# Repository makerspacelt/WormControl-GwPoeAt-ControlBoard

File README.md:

---

WormControl Gateway POE.AT

NOTE: This is only a prototype now, so things might not work and everything might change 

Basic target features:

* Compatibility with esphome and Home Assistant

Dev NOTE: before commit, run `./kibot.sh` to regenerate documentation, bom, gerbers and other assets.

* [schematics.pdf](gen/schematics.pdf)
* [pcb.pdf with dimensions](gen/pcb.pdf)
* [ibom.html](gen/single/ibom.html)

---

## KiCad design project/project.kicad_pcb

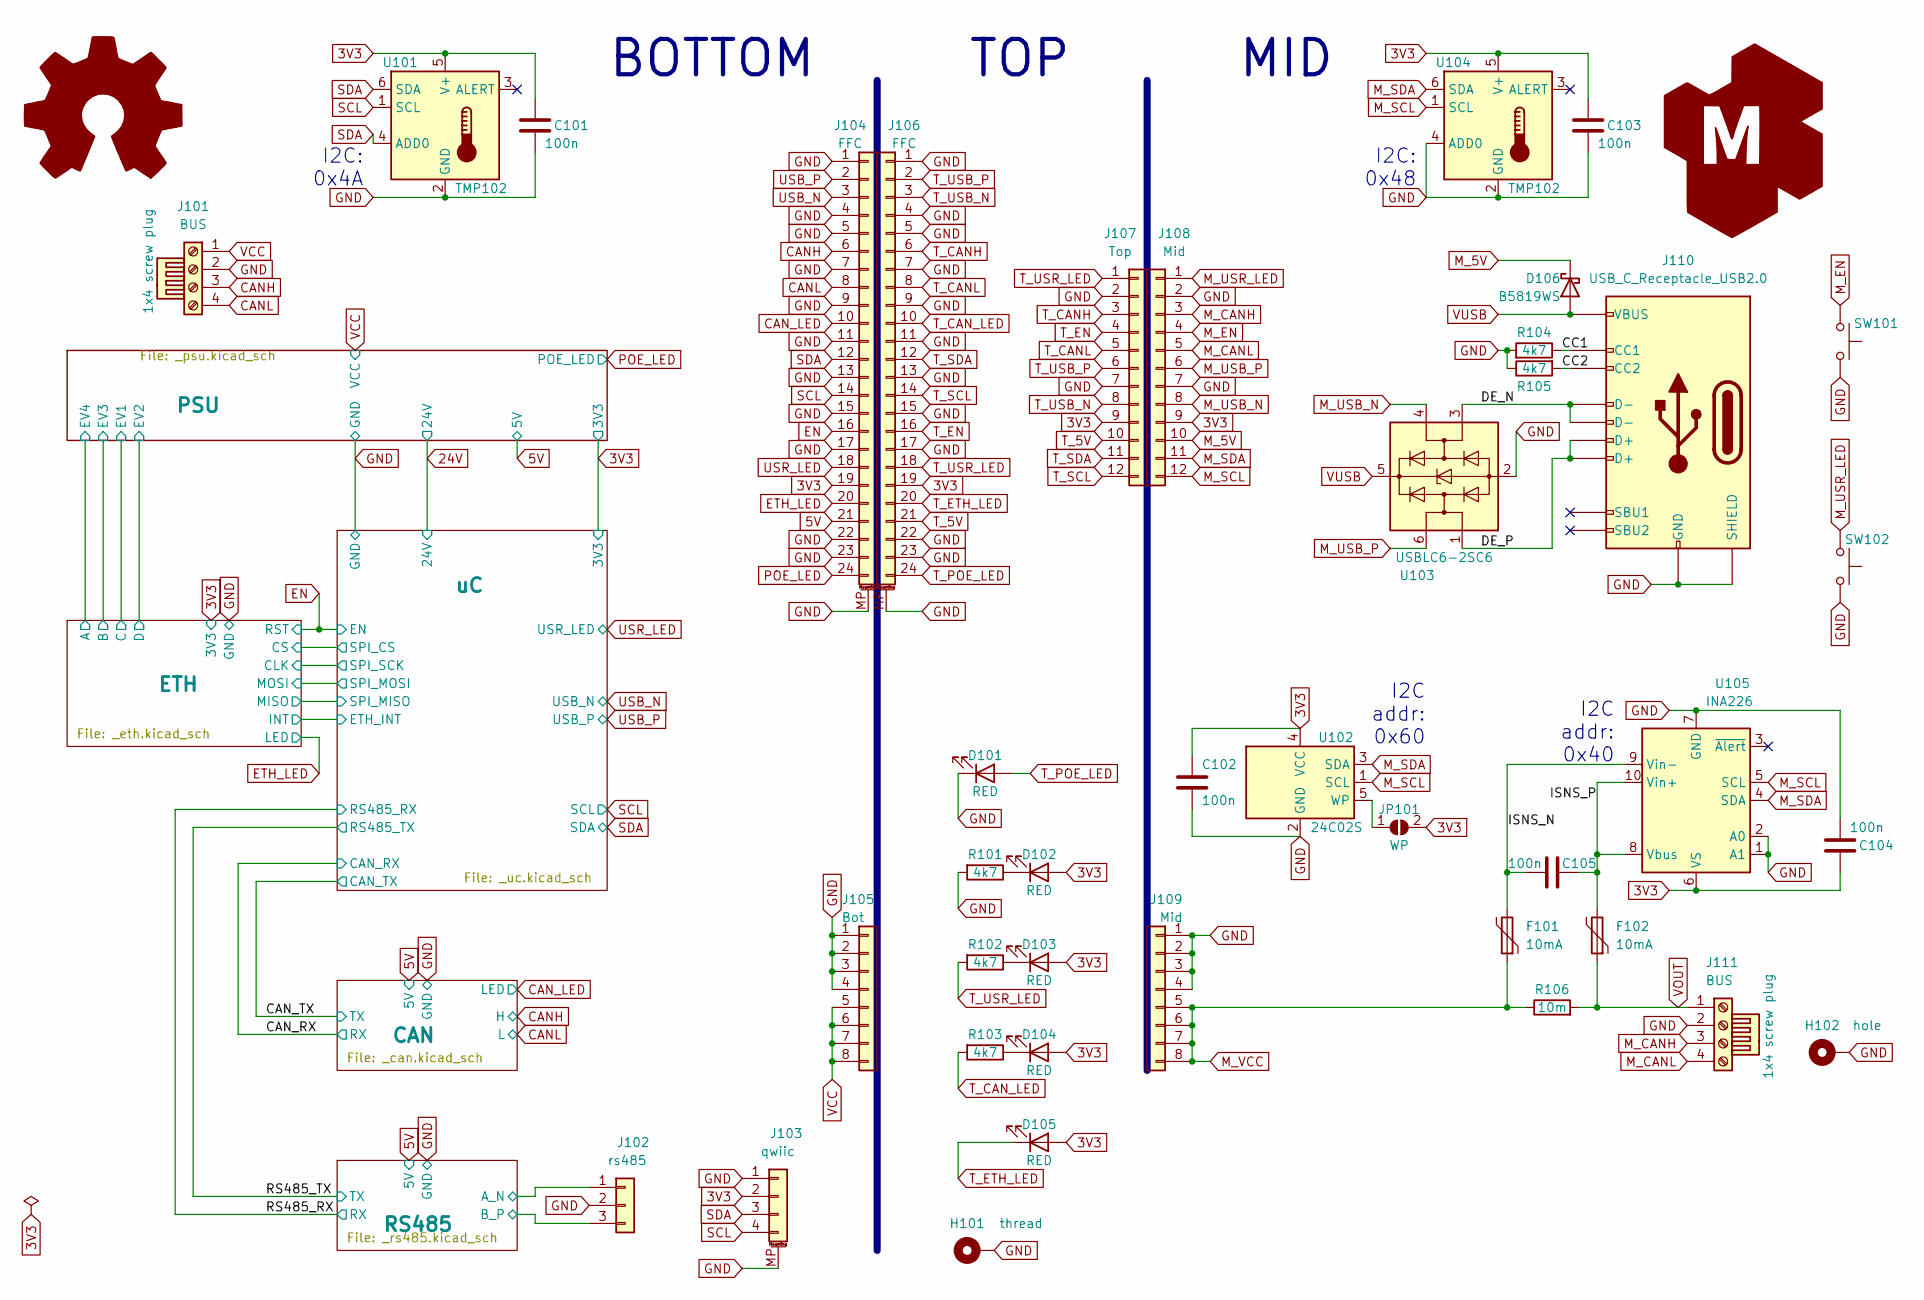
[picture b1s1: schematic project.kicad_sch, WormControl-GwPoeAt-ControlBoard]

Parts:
BOM101, BOM102: 1x4 screw plug; jlc-part-type E+
C101, C102, C103, C104, C105: 100n; C_0402_1005Metric_Pad0.74x0.62mm_HandSolder; jlc-part-type B+
D101, D102, D103, D104, D105: RED; LED_1206_3216Metric_ReverseMount; jlc-part-type E+
D106: B5819WS; D_SOD-323_HandSoldering; jlc-part-type B+
F101, F102: 10mA; Fuse_0805_2012Metric_Pad1.15x1.40mm_HandSolder; lcsc# C7472543
G101: Logo_Open_Hardware_Large; OSHW-Symbol_6.7x6mm_SilkScreen
G102: LOGO_KMS; logo_kms_small_silkscreen
H101: thread; post_m3x12.5mm; lcsc# C30182781
H102: hole; MountingHole_3.2mm_M3_Pad_Via
J101, J111: BUS; PhoenixContact_MCV_1,5_4-G-3.5_1x04_P3.50mm_Vertical; jlc-part-type E+
J102: rs485; JST_XH_B3B-XH-A_1x03_P2.50mm_Vertical; jlc-part-type ???
J103: qwiic; JST_SH_BM04B-SRSS-TB_1x04-1MP_P1.00mm_Vertical; jlc-part-type E+
J104, J106: FFC; AFC11-S24ICC-00; jlc-part-type E+
J105: Bot; JST_XH_B8B-XH-A_1x08_P2.50mm_Vertical; jlc-part-type ???
J107: Top; PinHeader_2x06_P2.54mm_Vertical_SMD; lcsc# C5160780
J108: Mid; PinSocket_2x06_P2.54mm_Vertical_SMD; lcsc# C3975151
J109: Mid; JST_XH_B8B-XH-A_1x08_P2.50mm_Vertical; jlc-part-type ???
J110: USB_C_Receptacle_USB2.0; USB_C_Receptacle_G-Switch_GT-USB-7082G; jlc-part-type E+
JP101: WP; SolderJumper-2_P1.3mm_Open_TrianglePad1.0x1.5mm
R101, R102, R103, R104, R105: 4k7; R_0402_1005Metric_Pad0.72x0.64mm_HandSolder; jlc-part-type B+
R106: 10m; R_1206_3216Metric_Pad1.30x1.75mm_HandSolder; jlc-part-type E+
SW101, SW102: 15mm; SW_SPST_15; jlc-part-type E+
U101, U104: TMP102; SOT-563; jlc-part-type E+
U102: 24C02S; SOT-23-5; jlc-part-type E+
U103: USBLC6-2SC6; SOT-23-6; jlc-part-type E+
U105: INA226; VSSOP-10_3x3mm_P0.5mm; jlc-part-type E+

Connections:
3V3: C101.1, C102.2, C103.1, C104.1, D102.2 (A), D103.2 (A), D104.2 (A), D105.2 (A), J103.2, J104.19, J106.19, J107.9, J108.9, JP101.2 (B), U101.5 (V+), U102.4 (VCC), U104.5 (V+), U105.6 (VS); also elsewhere on the board
5V: J104.21; also elsewhere on the board
/CC1: J110.A5 (CC1), R104.1
/CC2: J110.B5 (CC2), R105.2
/DE_N: J110.A7 (D-), J110.B7 (D-), U103.3 (I/O2)
/DE_P: J110.A6 (D+), J110.B6 (D+), U103.1 (I/O1)
/ISNS_N: C105.2, F101.2, U105.9 (Vin-)
/ISNS_P: C105.1, F102.2, U105.8 (Vbus), U105.10 (Vin+)
/RS485/A_N: J102.1; also elsewhere on the board
/RS485/B_P: J102.3; also elsewhere on the board
CANH: J101.3, J104.6; also elsewhere on the board
CANL: J101.4, J104.8; also elsewhere on the board
CAN_LED: J104.10; also elsewhere on the board
EN: J104.16; also elsewhere on the board
ETH_LED: J104.20; also elsewhere on the board
GND: C101.2, C102.1, C103.2, C104.2, D101.1 (K), H101.1, H102.1, J101.2, J102.2, J103.1, J103.MP (MountPin), J104.1, J104.4, J104.5, J104.7, J104.9, J104.11, J104.13, J104.15, J104.17, J104.22, J104.23, J104.MP (MountPin), J105.1, J105.2, J105.3, J105.4, J106.1, J106.4, J106.5, J106.7, J106.9, J106.11, J106.13, J106.15, J106.17, J106.22, J106.23, J106.MP (MountPin), J107.2, J107.7, J108.2, J108.7, J109.1, J109.2, J109.3, J109.4, J110.A1 (GND), J110.A12 (GND), J110.B1 (GND), J110.B12 (GND), J110.S1 (SHIELD), J111.2, R101.2, R104.2, R105.1, SW101.2, SW102.2, U101.2 (GND), U102.2 (GND), U103.2 (GND), U104.2 (GND), U104.4 (ADD0), U105.1 (A1), U105.2 (A0), U105.7 (GND); also elsewhere on the board
M_5V: D106.1 (K), J108.10
M_CANH: J108.3, J111.3
M_CANL: J108.5, J111.4
M_EN: J108.4, SW101.1
M_SCL: J108.12, U102.1 (SCL), U104.1 (SCL), U105.5 (SCL)
M_SDA: J108.11, U102.3 (SDA), U104.6 (SDA), U105.4 (SDA)
M_USB_N: J108.8, U103.4 (I/O2)
M_USB_P: J108.6, U103.6 (I/O1)
M_USR_LED: J108.1, SW102.1
M_VCC: F101.1, J109.5, J109.6, J109.7, J109.8, R106.1
unnamed: D102.1 (K), R101.1
unnamed: D103.1 (K), R102.1
unnamed: D104.1 (K), R103.1
unnamed: JP101.1 (A), U102.5 (WP)
POE_LED: J104.24; also elsewhere on the board
SCL: J103.4, J104.14, U101.1 (SCL); also elsewhere on the board
SDA: J103.3, J104.12, U101.4 (ADD0), U101.6 (SDA); also elsewhere on the board
T_5V: J106.21, J107.10
T_CANH: J106.6, J107.3
T_CANL: J106.8, J107.5
T_CAN_LED: J106.10, R103.2
T_EN: J106.16, J107.4
T_ETH_LED: D105.1 (K), J106.20
T_POE_LED: D101.2 (A), J106.24
T_SCL: J106.14, J107.12
T_SDA: J106.12, J107.11
T_USB_N: J106.3, J107.8
T_USB_P: J106.2, J107.6
T_USR_LED: J106.18, J107.1, R102.2
USB_N: J104.3; also elsewhere on the board
USB_P: J104.2; also elsewhere on the board
USR_LED: J104.18; also elsewhere on the board
VCC: J101.1, J105.5, J105.6, J105.7, J105.8; also elsewhere on the board
VOUT: F102.1, J111.1, R106.2
VUSB: D106.2 (A), J110.A4 (VBUS), J110.A9 (VBUS), J110.B4 (VBUS), J110.B9 (VBUS), U103.5 (VBUS)

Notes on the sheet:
I2C addr: 0x40
I2C addr: 0x60
I2C: 0x48
TOP
MID
I2C: 0x4A
BOTTOM

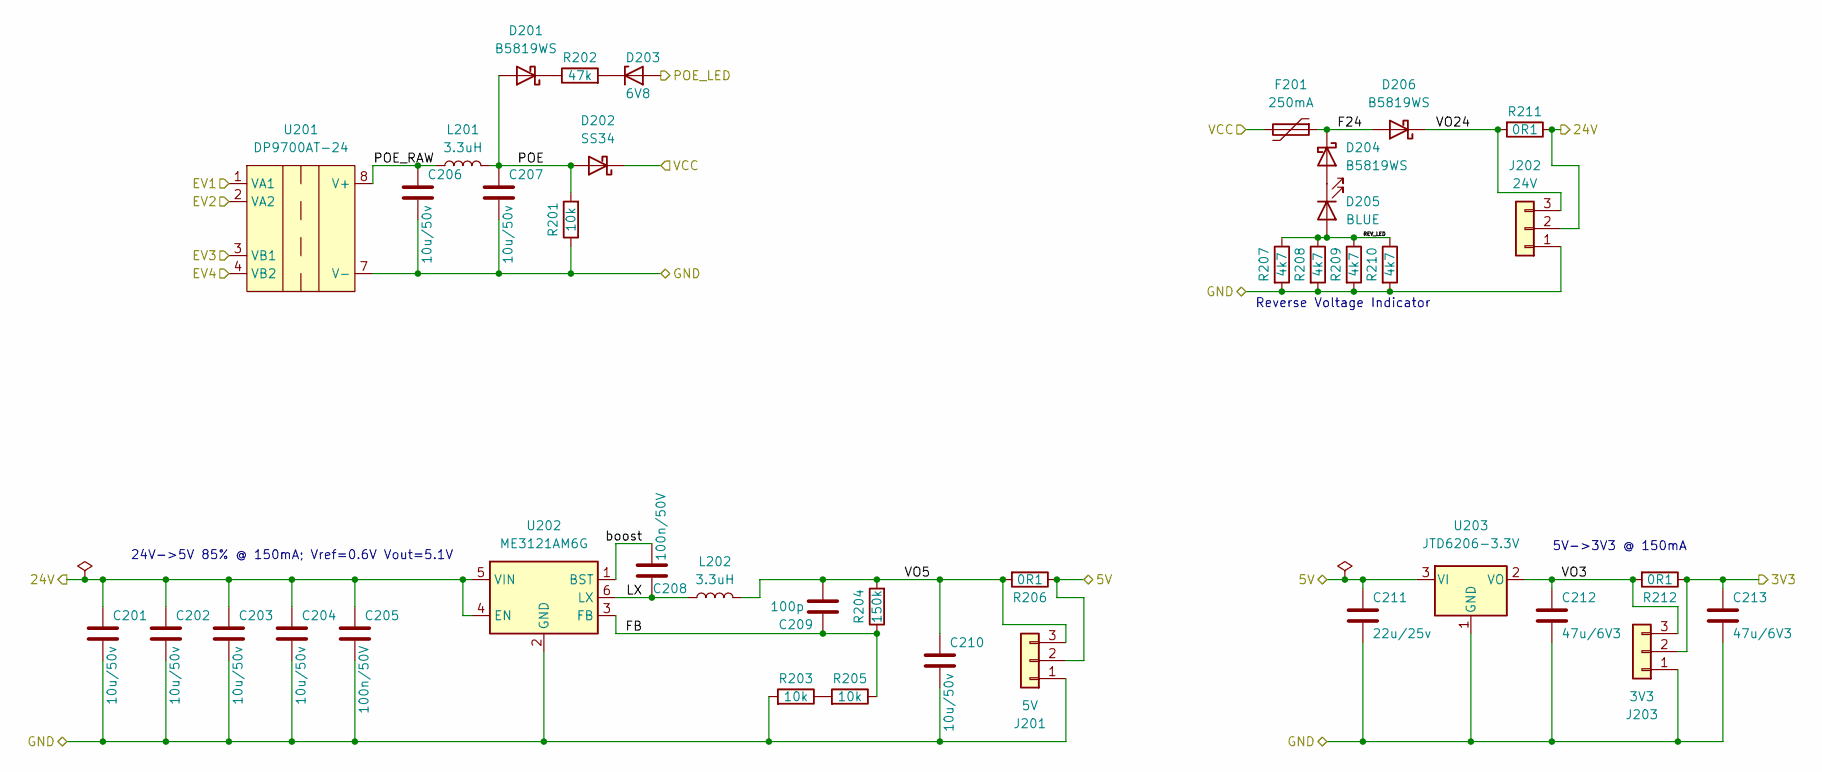
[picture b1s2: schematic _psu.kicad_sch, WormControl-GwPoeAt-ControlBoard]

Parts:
C201, C202, C203, C204, C206, C207, C210: 10u/50v; C_0805_2012Metric_Pad1.18x1.45mm_HandSolder; jlc-part-type B+
C205, C208: 100n/50V; C_0402_1005Metric_Pad0.74x0.62mm_HandSolder; jlc-part-type B+
C209: 100p; C_0805_2012Metric_Pad1.18x1.45mm_HandSolder; jlc-part-type B+
C211: 22u/25v; C_0805_2012Metric_Pad1.18x1.45mm_HandSolder; jlc-part-type B+
C212, C213: 47u/6V3; C_0805_2012Metric_Pad1.18x1.45mm_HandSolder; jlc-part-type B+
D201, D204, D206: B5819WS; D_SOD-323_HandSoldering; jlc-part-type B+
D202: SS34; D_SMA; jlc-part-type B+
D203: 6V8; D_SOD-323_HandSoldering; jlc-part-type E+
D205: BLUE; LED_0805_2012Metric_Pad1.15x1.40mm_HandSolder; jlc-part-type B+
F201: 250mA; Fuse_0805_2012Metric_Pad1.15x1.40mm_HandSolder; lcsc# C22378353
J201: 5V; PinHeader_1x03_P2.54mm_Vertical
J202: 24V; PinHeader_1x03_P2.54mm_Vertical
J203: 3V3; PinHeader_1x03_P2.54mm_Vertical
L201, L202: 3.3uH; L_1008_2520Metric_Pad1.43x2.20mm_HandSolder; jlc-part-type E+
R201, R203, R205: 10k; R_0805_2012Metric_Pad1.20x1.40mm_HandSolder; jlc-part-type B+
R202: 47k; R_0402_1005Metric_Pad0.72x0.64mm_HandSolder; jlc-part-type B+
R204: 150k; R_0805_2012Metric_Pad1.20x1.40mm_HandSolder; jlc-part-type B+
R206, R211, R212: 0R1; R_0805_2012Metric_Pad1.20x1.40mm_HandSolder; jlc-part-type E+
R207, R208, R209, R210: 4k7; R_0805_2012Metric_Pad1.20x1.40mm_HandSolder; jlc-part-type B+
U201: DP9700AT-24; DP9700AT; jlc-part-type E+
U202: ME3121AM6G; SOT-23-6; jlc-part-type E+
U203: JTD6206-3.3V; SOT-23; jlc-part-type B+

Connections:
3V3: C213.1, J203.2, R212.1; also elsewhere on the board
5V: C211.1, J201.2, R206.1, U203.3 (VI); also elsewhere on the board
24V: C201.1, C202.1, C203.1, C204.1, C205.1, J202.2, R211.1, U202.4 (EN), U202.5 (VIN); also elsewhere on the board
/ETH/A: U201.4 (VB2); also elsewhere on the board
/ETH/B: U201.3 (VB1); also elsewhere on the board
/ETH/C: U201.1 (VA1); also elsewhere on the board
/ETH/D: U201.2 (VA2); also elsewhere on the board
/PSU/F24: D204.1 (K), D206.2 (A), F201.1
/PSU/FB: C209.1, R204.1, R205.1, U202.3 (FB)
/PSU/LX: C208.2, L202.1, U202.6 (LX)
/PSU/POE: C207.1, D201.2 (A), D202.2 (A), L201.2, R201.2
/PSU/POE_RAW: C206.1, L201.1, U201.8 (V+)
/PSU/REV_LED: D205.2 (A), R207.1, R208.1, R209.1, R210.1
/PSU/VO3: C212.1, J203.3, R212.2, U203.2 (VO)
/PSU/VO5: C209.2, C210.1, J201.3, L202.2, R204.2, R206.2
/PSU/VO24: D206.1 (K), J202.3, R211.2
/PSU/boost: C208.1, U202.1 (BST)
GND: C201.2, C202.2, C203.2, C204.2, C205.2, C206.2, C207.2, C210.2, C211.2, C212.2, C213.2, J201.1, J202.1, J203.1, R201.1, R203.2, R207.2, R208.2, R209.2, R210.2, U201.7 (V-), U202.2 (GND), U203.1 (GND); also elsewhere on the board
unnamed: D201.1 (K), R202.1
unnamed: D203.1 (K), R202.2
unnamed: D204.2 (A), D205.1 (K)
unnamed: R203.1, R205.2
POE_LED: D203.2 (A); also elsewhere on the board
VCC: D202.1 (K), F201.2; also elsewhere on the board

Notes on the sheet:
24V->5V 85% @ 150mA; Vref=0.6V Vout=5.1V
5V->3V3 @ 150mA
Reverse Voltage Indicator

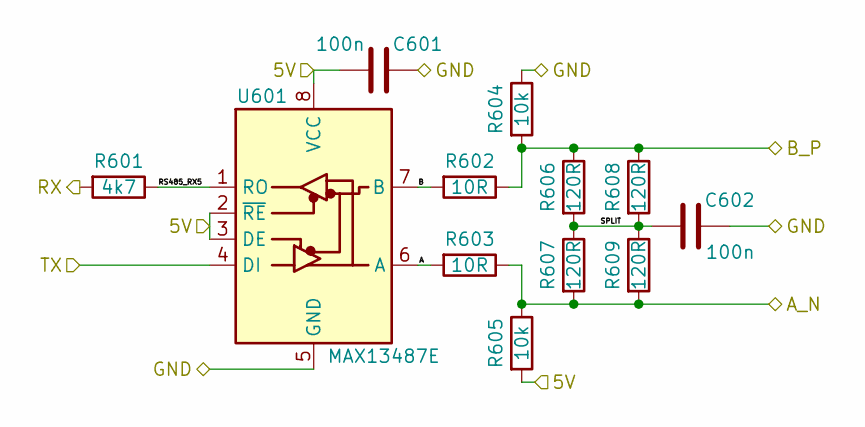
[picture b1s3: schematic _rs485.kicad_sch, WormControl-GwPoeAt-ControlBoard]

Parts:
C601, C602: 100n; C_0402_1005Metric_Pad0.74x0.62mm_HandSolder; jlc-part-type B+
R601: 4k7; R_0402_1005Metric_Pad0.72x0.64mm_HandSolder; jlc-part-type B+
R602, R603: 10R; R_0402_1005Metric_Pad0.72x0.64mm_HandSolder; jlc-part-type B+
R604, R605: 10k; R_0402_1005Metric_Pad0.72x0.64mm_HandSolder; jlc-part-type B+
R606, R607, R608, R609: 120R; R_0805_2012Metric_Pad1.20x1.40mm_HandSolder; jlc-part-type B+
U601: MAX13487E; SOIC-8_3.9x4.9mm_P1.27mm; jlc-part-type E+

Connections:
5V: C601.1, R605.2, U601.2 (~RE), U601.3 (DE), U601.8 (VCC); also elsewhere on the board
/RS485/A: R603.2, U601.6 (A)
/RS485/A_N: R603.1, R605.1, R607.2, R609.2; also elsewhere on the board
/RS485/B: R602.2, U601.7 (B)
/RS485/B_P: R602.1, R604.2, R606.1, R608.1; also elsewhere on the board
/RS485/RS485_RX5: R601.1, U601.1 (RO)
/RS485/SPLIT: C602.1, R606.2, R607.1, R608.2, R609.1
/RS485_RX: R601.2; also elsewhere on the board
/RS485_TX: U601.4 (DI); also elsewhere on the board
GND: C601.2, C602.2, R604.1, U601.5 (GND); also elsewhere on the board

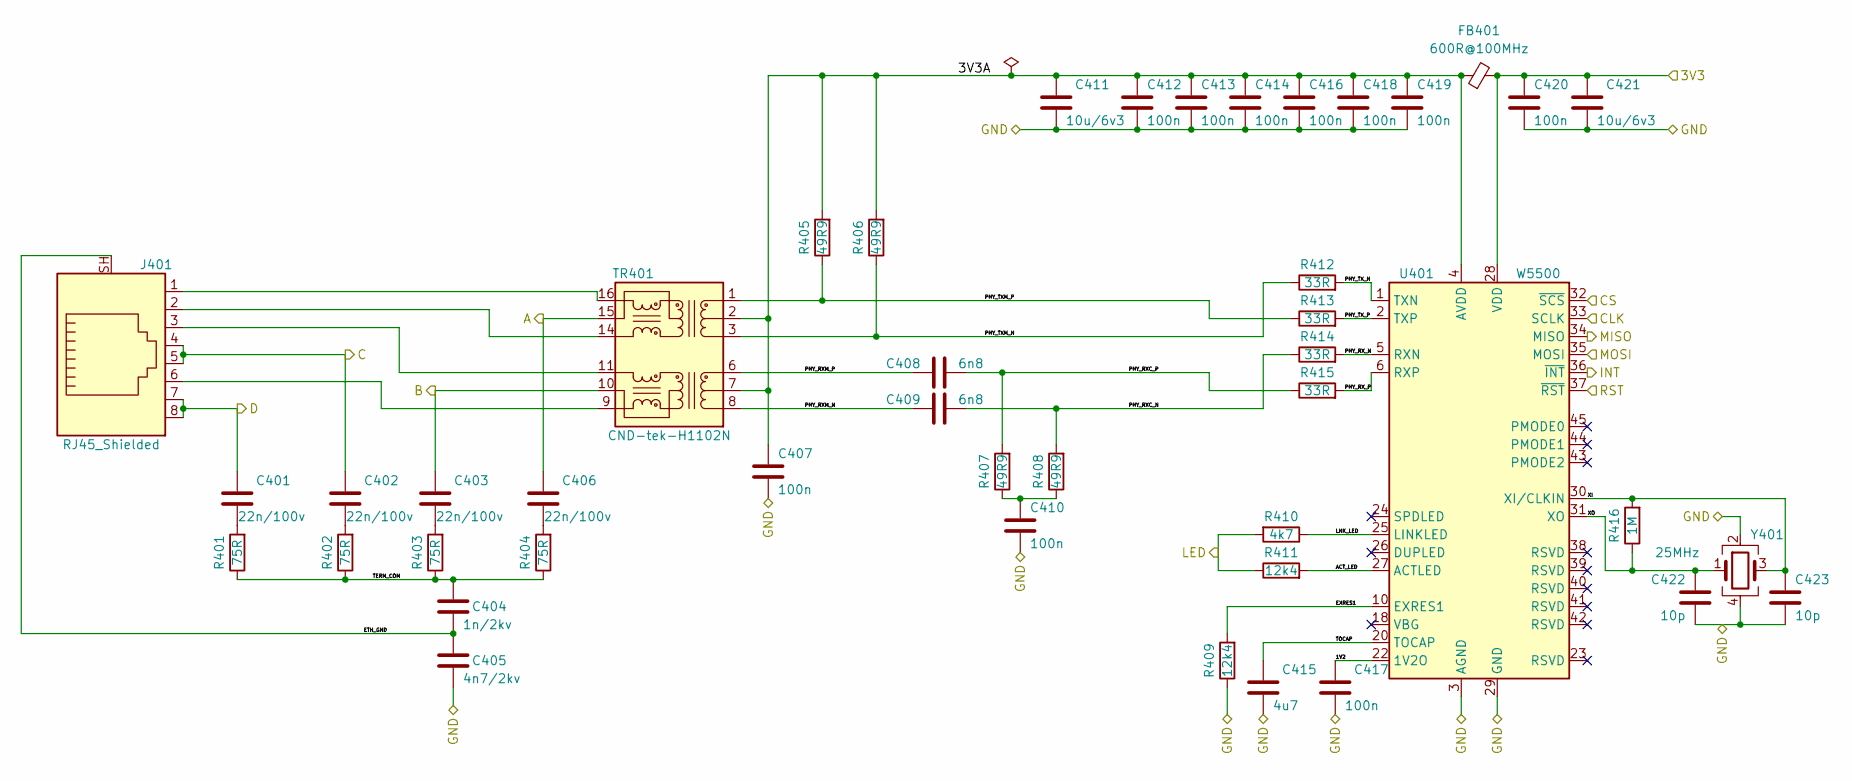
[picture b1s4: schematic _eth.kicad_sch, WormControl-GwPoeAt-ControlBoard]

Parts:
C401, C402, C403, C406: 22n/100v; C_0603_1608Metric_Pad1.08x0.95mm_HandSolder; jlc-part-type E+
C404: 1n/2kv; C_1206_3216Metric_Pad1.33x1.80mm_HandSolder; jlc-part-type B+
C405: 4n7/2kv; C_1206_3216Metric_Pad1.33x1.80mm_HandSolder; jlc-part-type E+
C407, C410, C412, C413, C414, C416, C417, C418, C419, C420: 100n; C_0402_1005Metric_Pad0.74x0.62mm_HandSolder; jlc-part-type B+
C408, C409: 6n8; C_0603_1608Metric_Pad1.08x0.95mm_HandSolder; jlc-part-type B+
C411, C421: 10u/6v3; C_0402_1005Metric_Pad0.74x0.62mm_HandSolder; jlc-part-type B+
C415: 4u7; C_0402_1005Metric_Pad0.74x0.62mm_HandSolder; jlc-part-type B+
C422, C423: 10p; C_0402_1005Metric_Pad0.74x0.62mm_HandSolder; jlc-part-type B+
FB401: 600R@100MHz; L_0805_2012Metric_Pad1.05x1.20mm_HandSolder; jlc-part-type B+
J401: RJ45_Shielded; RJ45_FG_RJ-064-1; jlc-part-type E+
R401, R402, R403, R404: 75R; R_0402_1005Metric_Pad0.72x0.64mm_HandSolder; jlc-part-type ER+
R405, R406, R407, R408: 49R9; R_0402_1005Metric_Pad0.72x0.64mm_HandSolder; jlc-part-type B+
R409, R411: 12k4; R_0402_1005Metric_Pad0.72x0.64mm_HandSolder; jlc-part-type E+
R410: 4k7; R_0402_1005Metric_Pad0.72x0.64mm_HandSolder; jlc-part-type B+
R412, R413, R414, R415: 33R; R_0402_1005Metric_Pad0.72x0.64mm_HandSolder; jlc-part-type B+
R416: 1M; R_0402_1005Metric_Pad0.72x0.64mm_HandSolder; jlc-part-type B+
TR401: CND-tek-H1102N; Transformer_Ethernet_SO-16_7.11x12.7mm; jlc-part-type E+
U401: W5500; LQFP-48_7x7mm_P0.5mm; jlc-part-type E+
Y401: 25MHz; Crystal_SMD_2016-4Pin_2.0x1.6mm; jlc-part-type E+

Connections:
3V3: C420.1, C421.1, FB401.2, U401.28 (VDD); also elsewhere on the board
/ETH/1V2: C417.1, U401.22 (1V2O)
/ETH/3V3A: C407.1, C411.1, C412.1, C413.1, C414.1, C416.1, C418.1, C419.1, FB401.1, R405.2, R406.2, TR401.2 (C_TD), TR401.7 (C_RD), U401.4 (AVDD), U401.8 (AVDD), U401.11 (AVDD), U401.15 (AVDD), U401.17 (AVDD), U401.21 (AVDD)
/ETH/A: C406.1, TR401.15 (C_TX); also elsewhere on the board
/ETH/ACT_LED: R411.2, U401.27 (ACTLED)
/ETH/B: C403.1, TR401.10 (C_RX); also elsewhere on the board
/ETH/C: C402.1, J401.4, J401.5; also elsewhere on the board
/ETH/CLK: U401.33 (SCLK); also elsewhere on the board
/ETH/CS: U401.32 (~SCS); also elsewhere on the board
/ETH/D: C401.1, J401.7, J401.8; also elsewhere on the board
/ETH/ETH_GND: C404.2, C405.1, J401.SH
/ETH/EXRES1: R409.2, U401.10 (EXRES1)
/ETH/INT: U401.36 (~INT); also elsewhere on the board
/ETH/LNK_LED: R410.1, U401.25 (LINKLED)
/ETH/MISO: U401.34 (MISO); also elsewhere on the board
/ETH/MOSI: U401.35 (MOSI); also elsewhere on the board
/ETH/PHY_RXC_N: C409.2, R408.2, R414.1
/ETH/PHY_RXC_P: C408.2, R407.2, R415.1
/ETH/PHY_RXM_N: C409.1, TR401.8 (RD-)
/ETH/PHY_RXM_P: C408.1, TR401.6 (RD+)
/ETH/PHY_RX_N: R414.2, U401.5 (RXN)
/ETH/PHY_RX_P: R415.2, U401.6 (RXP)
/ETH/PHY_TXM_N: R406.1, R412.1, TR401.3 (TD-)
/ETH/PHY_TXM_P: R405.1, R413.1, TR401.1 (TD+)
/ETH/PHY_TX_N: R412.2, U401.1 (TXN)
/ETH/PHY_TX_P: R413.2, U401.2 (TXP)
/ETH/TERM_COM: C404.1, R401.1, R402.1, R403.1, R404.1
/ETH/TOCAP: C415.1, U401.20 (TOCAP)
/ETH/XI: C423.1, R416.2, U401.30 (XI/CLKIN), Y401.3
/ETH/XO: C422.1, R416.1, U401.31 (XO), Y401.1
EN: U401.37 (~RST); also elsewhere on the board
ETH_LED: R410.2, R411.1; also elsewhere on the board
GND: C405.2, C407.2, C410.2, C411.2, C412.2, C413.2, C414.2, C415.2, C416.2, C417.2, C418.2, C419.2, C420.2, C421.2, C422.2, C423.2, R409.1, U401.3 (AGND), U401.9 (AGND), U401.14 (AGND), U401.16 (AGND), U401.19 (AGND), U401.29 (GND), U401.48 (AGND), Y401.2, Y401.4; also elsewhere on the board
unnamed: C401.2, R401.2
unnamed: C402.2, R402.2
unnamed: C403.2, R403.2
unnamed: C406.2, R404.2
unnamed: C410.1, R407.1, R408.1
unnamed: J401.1, TR401.16 (TX+)
unnamed: J401.2, TR401.14 (TX-)
unnamed: J401.3, TR401.11 (RX+)
unnamed: J401.6, TR401.9 (RX-)

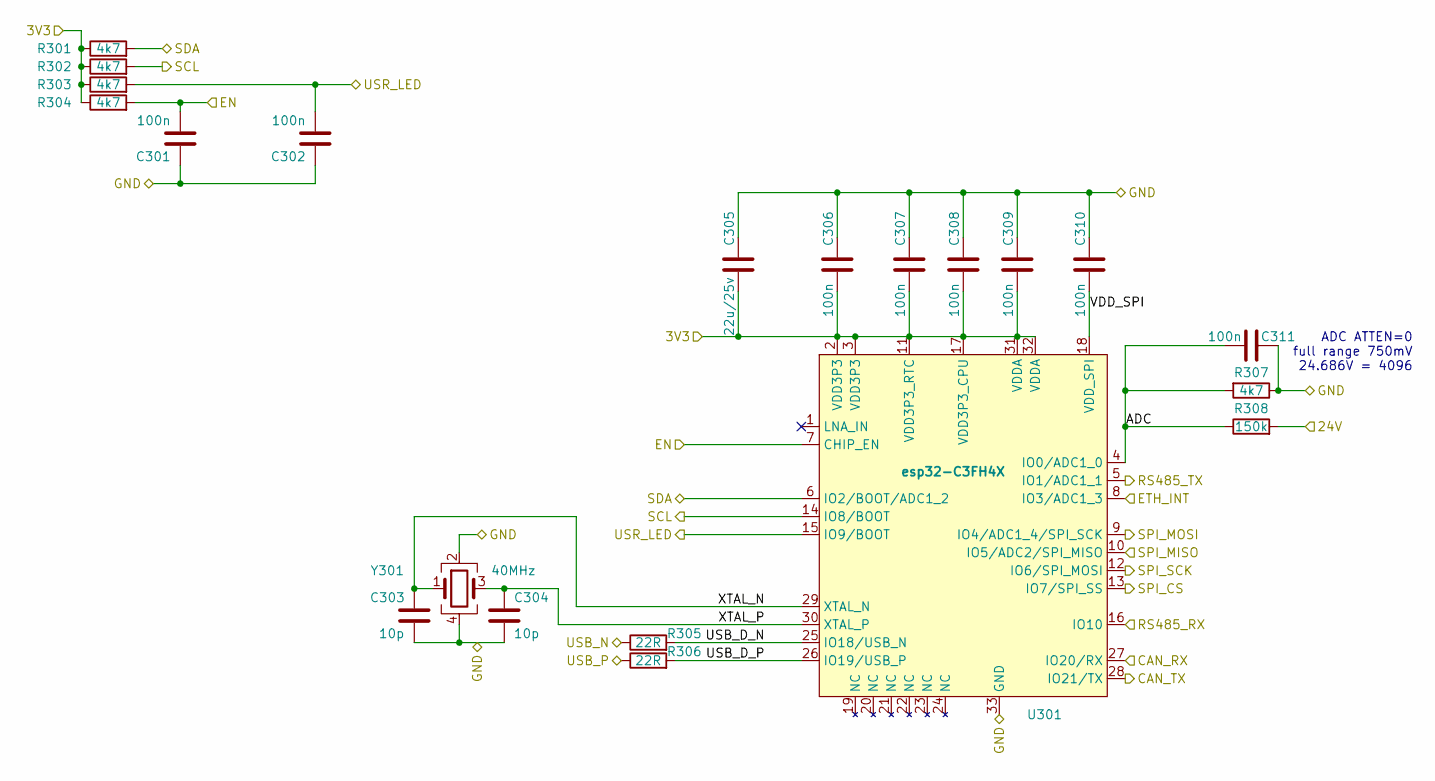
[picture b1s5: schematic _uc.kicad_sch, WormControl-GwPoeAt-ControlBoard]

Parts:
C301, C302, C306, C307, C308, C309, C310, C311: 100n; C_0402_1005Metric_Pad0.74x0.62mm_HandSolder; jlc-part-type B+
C303, C304: 10p; C_0402_1005Metric_Pad0.74x0.62mm_HandSolder; jlc-part-type B+
C305: 22u/25v; C_0805_2012Metric_Pad1.18x1.45mm_HandSolder; jlc-part-type B+
R301, R302, R303, R304, R307: 4k7; R_0402_1005Metric_Pad0.72x0.64mm_HandSolder; jlc-part-type B+
R305, R306: 22R; R_0402_1005Metric_Pad0.72x0.64mm_HandSolder; jlc-part-type B+
R308: 150k; R_0805_2012Metric_Pad1.20x1.40mm_HandSolder; jlc-part-type B+
U301: esp32-C3FH4X; QFN-32-1EP_5x5mm_P0.5mm_EP3.65x3.65mm; jlc-part-type E+
Y301: 40MHz; Crystal_SMD_2016-4Pin_2.0x1.6mm; jlc-part-type E+

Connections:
3V3: C305.2, C306.1, C307.1, C308.1, C309.1, R301.1, R302.1, R303.1, R304.1, U301.2 (VDD3P3), U301.3 (VDD3P3), U301.11 (VDD3P3_RTC), U301.17 (VDD3P3_CPU), U301.31 (VDDA), U301.32 (VDDA); also elsewhere on the board
24V: R308.2; also elsewhere on the board
/uC/ADC: C311.1, R307.2, R308.1, U301.4 (IO0/ADC1_0); also elsewhere on the board
/uC/USB_D_N: R305.2, U301.25 (IO18/USB_N); also elsewhere on the board
/uC/USB_D_P: R306.2, U301.26 (IO19/USB_P); also elsewhere on the board
/uC/VDD_SPI: C310.1, U301.18 (VDD_SPI); also elsewhere on the board
/uC/XTAL_N: C303.1, U301.29 (XTAL_N), Y301.1; also elsewhere on the board
/uC/XTAL_P: C304.1, U301.30 (XTAL_P), Y301.3; also elsewhere on the board
EN: C301.2, R304.2, U301.7 (CHIP_EN); also elsewhere on the board
GND: C301.1, C302.1, C303.2, C304.2, C305.1, C306.2, C307.2, C308.2, C309.2, C310.2, C311.2, R307.1, U301.33 (GND), Y301.2, Y301.4; also elsewhere on the board
SCL: R302.2, U301.14 (IO8/BOOT); also elsewhere on the board
SDA: R301.2, U301.6 (IO2/BOOT/ADC1_2); also elsewhere on the board
USB_N: R305.1; also elsewhere on the board
USB_P: R306.1; also elsewhere on the board
USR_LED: C302.2, R303.2, U301.15 (IO9/BOOT); also elsewhere on the board

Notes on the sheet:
ADC ATTEN=0 full range 750mV 24.686V = 4096

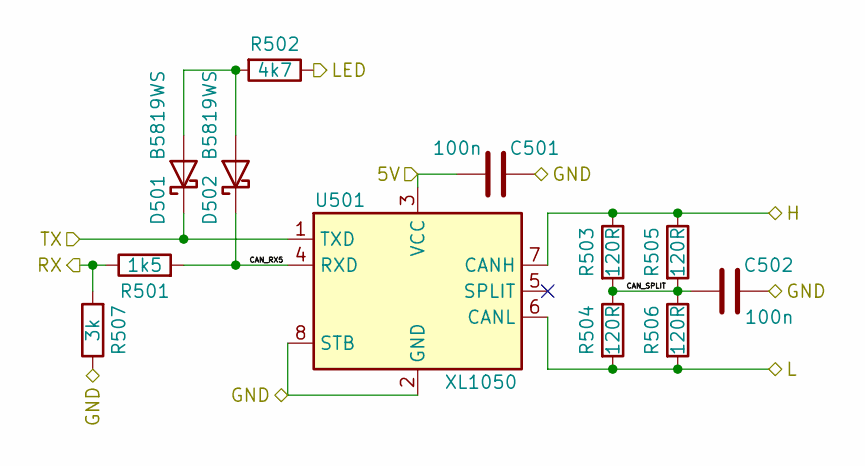
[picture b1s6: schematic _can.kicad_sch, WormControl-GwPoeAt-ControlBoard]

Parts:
C501, C502: 100n; C_0402_1005Metric_Pad0.74x0.62mm_HandSolder; jlc-part-type B+
D501, D502: B5819WS; D_SOD-323_HandSoldering; jlc-part-type B+
R501: 1k5; R_0402_1005Metric_Pad0.72x0.64mm_HandSolder; jlc-part-type B+
R502: 4k7; R_0402_1005Metric_Pad0.72x0.64mm_HandSolder; jlc-part-type B+
R503, R504, R505, R506: 120R; R_0805_2012Metric_Pad1.20x1.40mm_HandSolder; jlc-part-type B+
R507: 3k; R_0402_1005Metric_Pad0.72x0.64mm_HandSolder; jlc-part-type B+
U501: XL1050; SOIC-8_3.9x4.9mm_P1.27mm; jlc-part-type E+

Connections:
5V: C501.1, U501.3 (VCC); also elsewhere on the board
/CAN/CAN_RX5: D502.1 (K), R501.2, U501.4 (RXD)
/CAN/CAN_SPLIT: C502.1, R503.2, R504.1, R505.2, R506.1
/CAN_RX: R501.1, R507.2; also elsewhere on the board
/CAN_TX: D501.1 (K), U501.1 (TXD); also elsewhere on the board
CANH: R503.1, R505.1, U501.7 (CANH); also elsewhere on the board
CANL: R504.2, R506.2, U501.6 (CANL); also elsewhere on the board
CAN_LED: R502.1; also elsewhere on the board
GND: C501.2, C502.2, R507.1, U501.2 (GND), U501.8 (STB); also elsewhere on the board
unnamed: D501.2 (A), D502.2 (A), R502.2
